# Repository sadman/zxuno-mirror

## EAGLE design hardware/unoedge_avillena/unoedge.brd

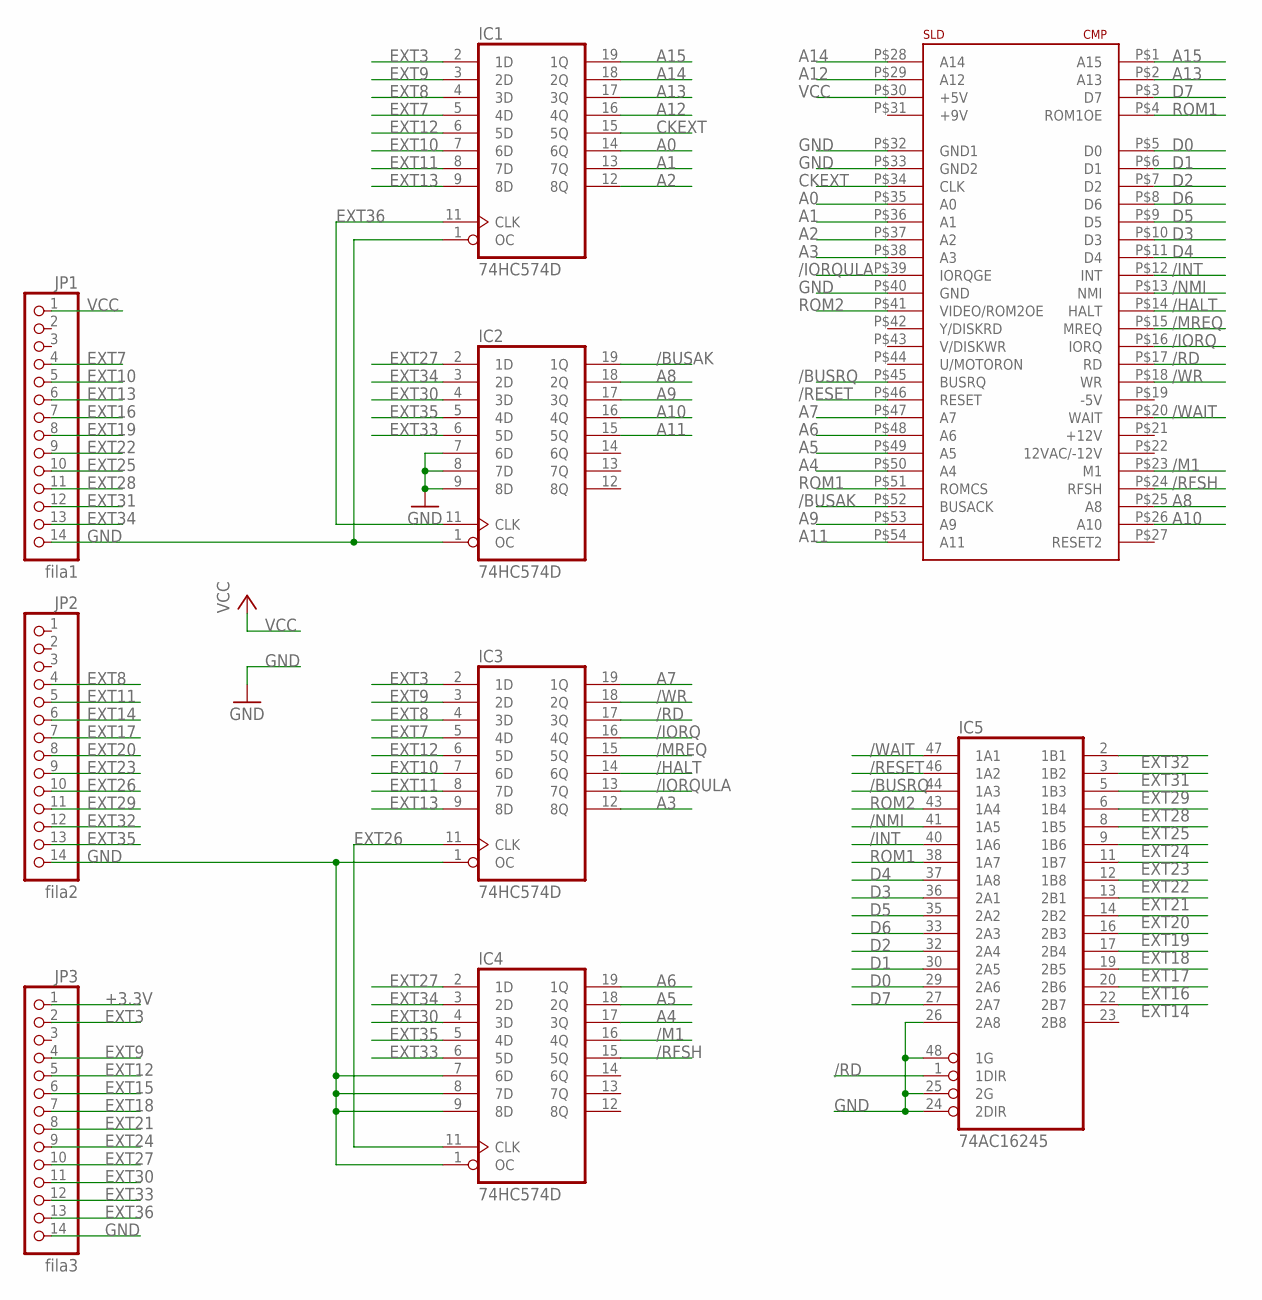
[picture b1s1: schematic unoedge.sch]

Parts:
IC1, IC2, IC3, IC4: 74HC574D; SO20W
IC5: 74AC16245; SSOP48DL
JP1: fila1; 1X14
JP2: fila2; 1X14
JP3: fila3; 1X14
U$2: CONECTOR_EDGE_LADO_SPECTRUM; CONECTOR_LADO_SPECTRUM

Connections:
+3.3V: JP3.1
/BUSAK: IC2.19 (1Q), U$2.P$52 (BUSACK)
/BUSRQ: IC5.44 (1A3), U$2.P$45 (BUSRQ)
/HALT: IC3.14 (6Q), U$2.P$14 (HALT)
/INT: IC5.40 (1A6), U$2.P$12 (INT)
/IORQ: IC3.16 (4Q), U$2.P$16 (IORQ)
/IORQULA: IC3.13 (7Q), U$2.P$39 (IORQGE)
/M1: IC4.16 (4Q), U$2.P$23 (M1)
/MREQ: IC3.15 (5Q), U$2.P$15 (MREQ)
/NMI: IC5.41 (1A5), U$2.P$13 (NMI)
/RD: IC3.17 (3Q), IC5.1 (1DIR), U$2.P$17 (RD)
/RESET: IC5.46 (1A2), U$2.P$46 (RESET)
/RFSH: IC4.15 (5Q), U$2.P$24 (RFSH)
/WAIT: IC5.47 (1A1), U$2.P$20 (WAIT)
/WR: IC3.18 (2Q), U$2.P$18 (WR)
A0: IC1.14 (6Q), U$2.P$35 (A0)
A1: IC1.13 (7Q), U$2.P$36 (A1)
A2: IC1.12 (8Q), U$2.P$37 (A2)
A3: IC3.12 (8Q), U$2.P$38 (A3)
A4: IC4.17 (3Q), U$2.P$50 (A4)
A5: IC4.18 (2Q), U$2.P$49 (A5)
A6: IC4.19 (1Q), U$2.P$48 (A6)
A7: IC3.19 (1Q), U$2.P$47 (A7)
A8: IC2.18 (2Q), U$2.P$25 (A8)
A9: IC2.17 (3Q), U$2.P$53 (A9)
A10: IC2.16 (4Q), U$2.P$26 (A10)
A11: IC2.15 (5Q), U$2.P$54 (A11)
A12: IC1.16 (4Q), U$2.P$29 (A12)
A13: IC1.17 (3Q), U$2.P$2 (A13)
A14: IC1.18 (2Q), U$2.P$28 (A14)
A15: IC1.19 (1Q), U$2.P$1 (A15)
CKEXT: IC1.15 (5Q), U$2.P$34 (CLK)
D0: IC5.29 (2A6), U$2.P$5 (D0)
D1: IC5.30 (2A5), U$2.P$6 (D1)
D2: IC5.32 (2A4), U$2.P$7 (D2)
D3: IC5.36 (2A1), U$2.P$10 (D3)
D4: IC5.37 (1A8), U$2.P$11 (D4)
D5: IC5.35 (2A2), U$2.P$9 (D5)
D6: IC5.33 (2A3), U$2.P$8 (D6)
D7: IC5.27 (2A7), U$2.P$3 (D7)
EXT3: IC1.2 (1D), IC3.2 (1D), JP3.2
EXT7: IC1.5 (4D), IC3.5 (4D), JP1.4
EXT8: IC1.4 (3D), IC3.4 (3D), JP2.4
EXT9: IC1.3 (2D), IC3.3 (2D), JP3.4
EXT10: IC1.7 (6D), IC3.7 (6D), JP1.5
EXT11: IC1.8 (7D), IC3.8 (7D), JP2.5
EXT12: IC1.6 (5D), IC3.6 (5D), JP3.5
EXT13: IC1.9 (8D), IC3.9 (8D), JP1.6
EXT14: IC5.22 (2B7), JP2.6
EXT15: JP3.6
EXT16: IC5.20 (2B6), JP1.7
EXT17: IC5.19 (2B5), JP2.7
EXT18: IC5.17 (2B4), JP3.7
EXT19: IC5.16 (2B3), JP1.8
EXT20: IC5.14 (2B2), JP2.8
EXT21: IC5.13 (2B1), JP3.8
EXT22: IC5.12 (1B8), JP1.9
EXT23: IC5.11 (1B7), JP2.9
EXT24: IC5.9 (1B6), JP3.9
EXT25: IC5.8 (1B5), JP1.10
EXT26: IC3.11 (CLK), IC4.11 (CLK), JP2.10
EXT27: IC2.2 (1D), IC4.2 (1D), JP3.10
EXT28: IC5.6 (1B4), JP1.11
EXT29: IC5.5 (1B3), JP2.11
EXT30: IC2.4 (3D), IC4.4 (3D), JP3.11
EXT31: IC5.3 (1B2), JP1.12
EXT32: IC5.2 (1B1), JP2.12
EXT33: IC2.6 (5D), IC4.6 (5D), JP3.12
EXT34: IC2.3 (2D), IC4.3 (2D), JP1.13
EXT35: IC2.5 (4D), IC4.5 (4D), JP2.13
EXT36: IC1.11 (CLK), IC2.11 (CLK), JP3.13
GND: IC1.1 (OC), IC1.10 (GND), IC2.1 (OC), IC2.7 (6D), IC2.8 (7D), IC2.9 (8D), IC2.10 (GND), IC3.1 (OC), IC3.10 (GND), IC4.1 (OC), IC4.7 (6D), IC4.8 (7D), IC4.9 (8D), IC4.10 (GND), IC5.4 (GND), IC5.10 (GND), IC5.15 (GND), IC5.21 (GND), IC5.24 (2DIR), IC5.25 (2G), IC5.26 (2A8), IC5.28 (GND), IC5.34 (GND), IC5.39 (GND), IC5.45 (GND), IC5.48 (1G), JP1.14, JP2.14, JP3.14, U$2.P$32 (GND1), U$2.P$33 (GND2), U$2.P$40 (GND)
ROM1: IC5.38 (1A7), U$2.P$4 (ROM1OE), U$2.P$51 (ROMCS)
ROM2: IC5.43 (1A4), U$2.P$41 (VIDEO/ROM2OE)
VCC: IC1.20 (VCC), IC2.20 (VCC), IC3.20 (VCC), IC4.20 (VCC), IC5.7 (VCC), IC5.18 (VCC), IC5.31 (VCC), IC5.42 (VCC), JP1.1, U$2.P$30 (+5V)

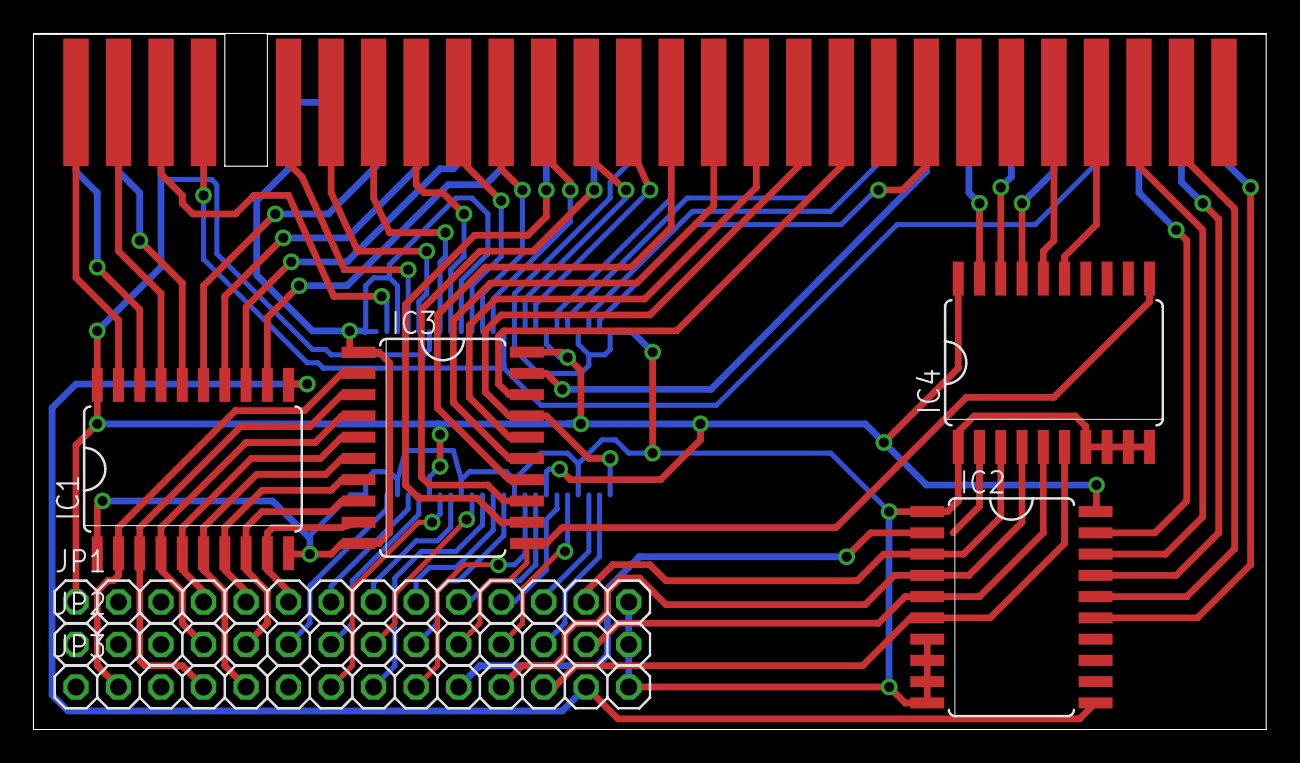
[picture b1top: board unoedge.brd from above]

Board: 2 copper layers, 73.7 x 41.6 mm, 9 parts (1 on the bottom side), 73 nets.

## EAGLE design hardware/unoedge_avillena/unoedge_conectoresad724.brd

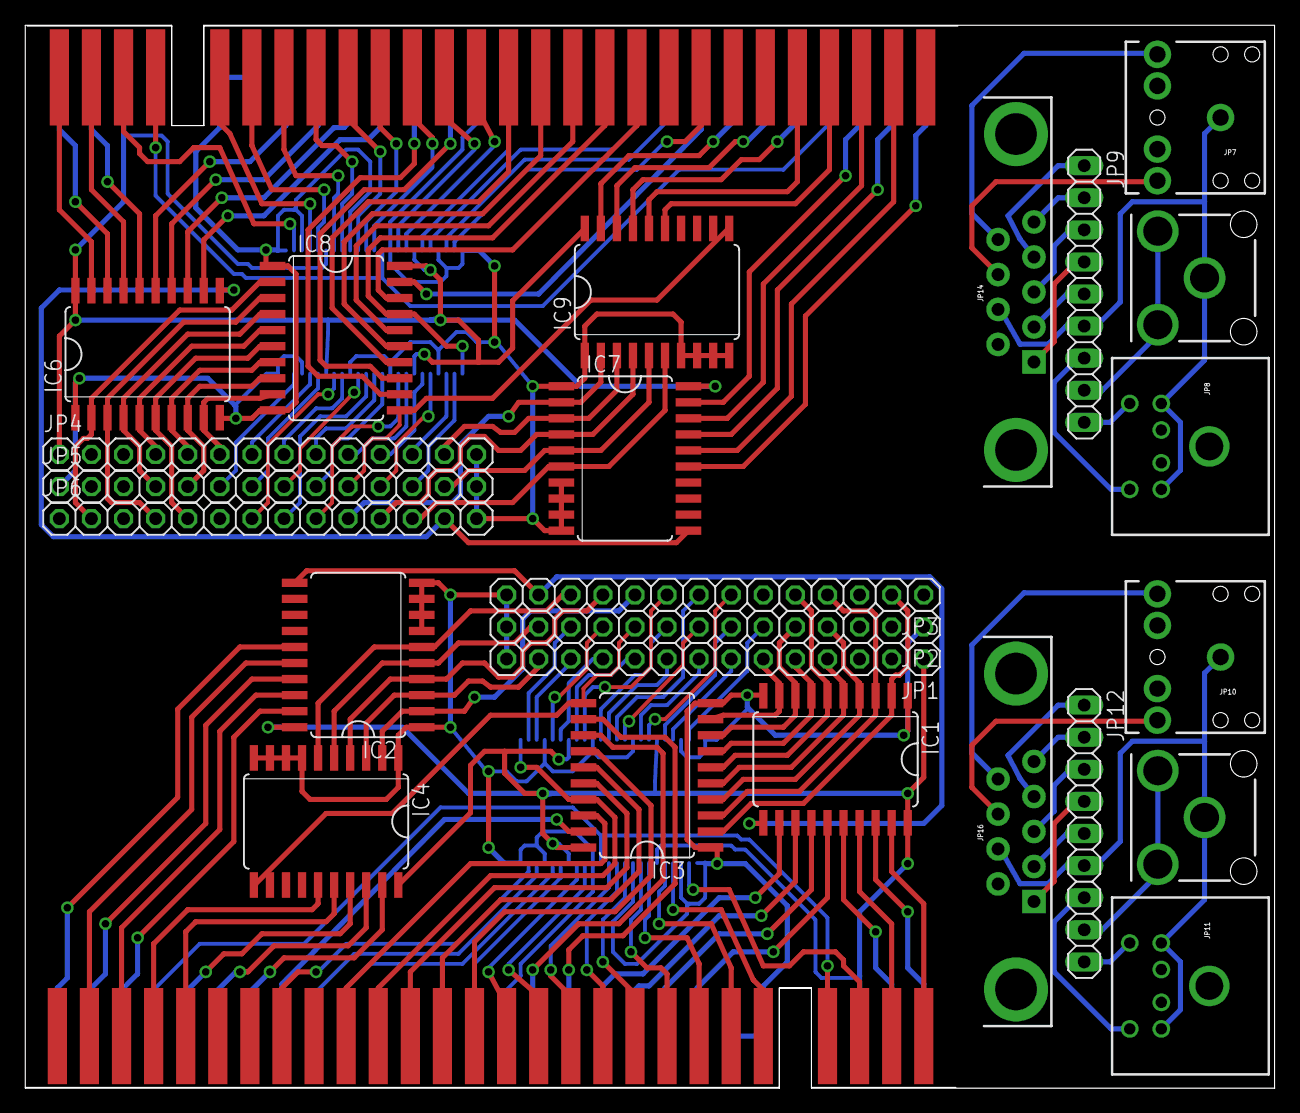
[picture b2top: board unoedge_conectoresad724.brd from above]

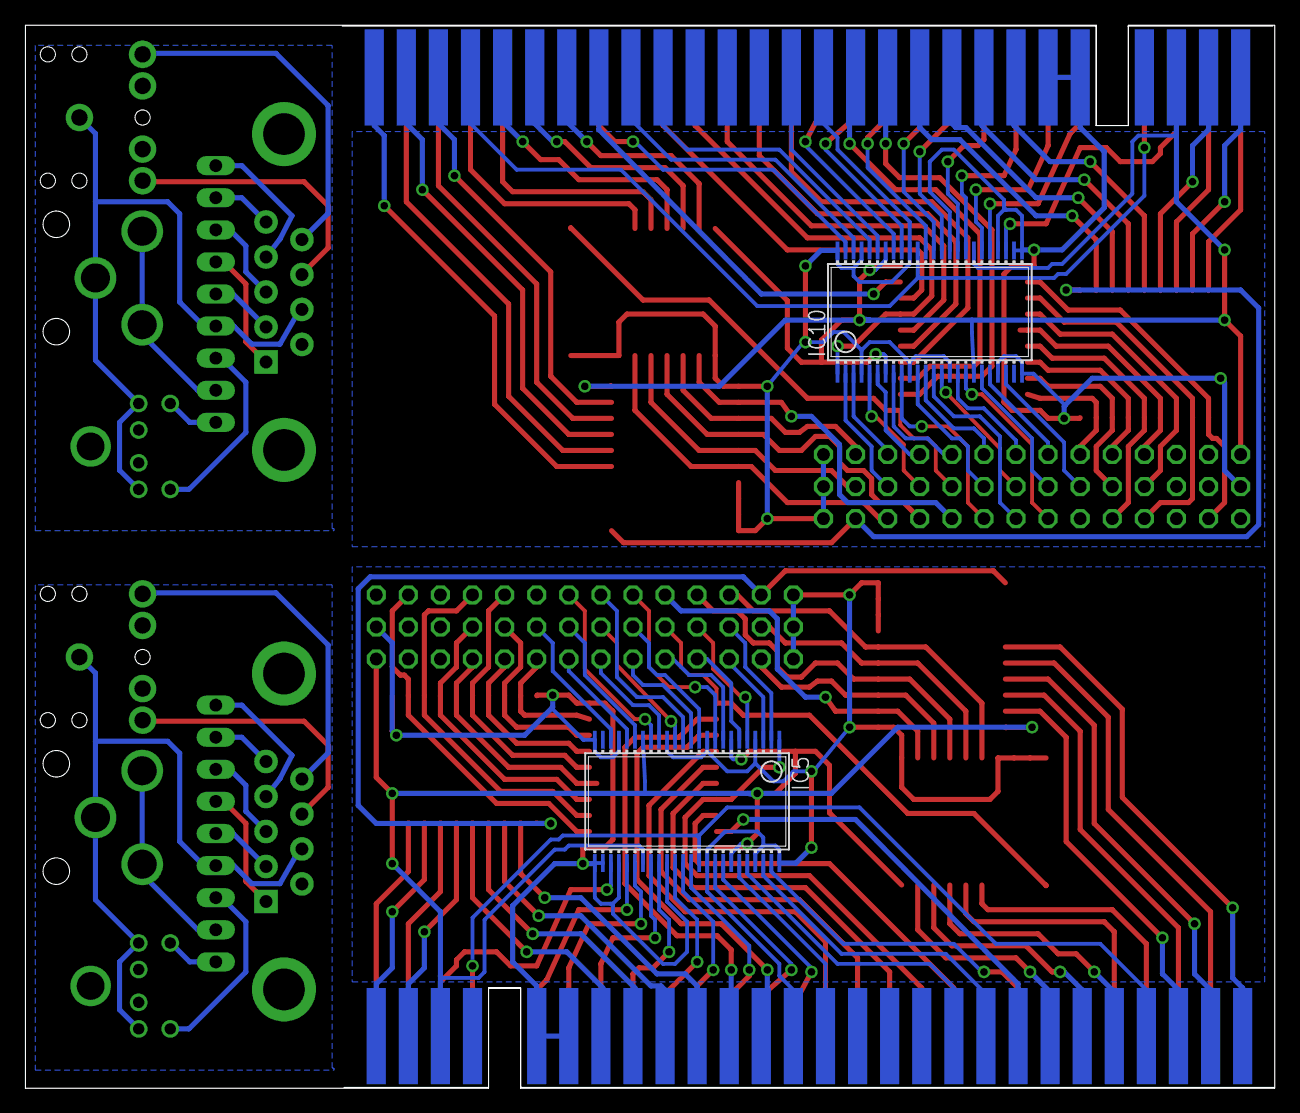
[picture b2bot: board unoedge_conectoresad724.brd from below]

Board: 2 copper layers, 98.9 x 84.1 mm, 28 parts (2 on the bottom side), 168 nets.

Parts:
IC1, IC2, IC3, IC4, IC6, IC7, IC8, IC9: 74HC574D; SO20W
IC5, IC10: 74AC16245; SSOP48DL
JP1, JP4: fila1; 1X14
JP2, JP5: fila2; 1X14
JP3, JP6: fila3; 1X14
JP7, JP10: AUDIO-JACK
JP8, JP11: MINI-DIN6PTH; MINI-DIN6
JP9, JP12: 1X09
JP13, JP15: RCA
JP14, JP16: DB9_MALE
U$1, U$2: CONECTOR_EDGE_LADO_SPECTRUM; CONECTOR_LADO_SPECTRUM

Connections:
/BUSAK: IC2.19, U$2.P$52
/BUSAK1: IC7.19, U$1.P$52
/BUSRQ: IC5.44, U$2.P$45
/BUSRQ1: IC10.44, U$1.P$45
/HALT: IC3.14, U$2.P$14
/HALT1: IC8.14, U$1.P$14
/INT: IC5.40, U$2.P$12
/INT1: IC10.40, U$1.P$12
/IORQ: IC3.16, U$2.P$16
/IORQ1: IC8.16, U$1.P$16
/IORQULA: IC3.13, U$2.P$39
/IORQULA1: IC8.13, U$1.P$39
/M1: IC4.16, U$2.P$23
/M2: IC9.16, U$1.P$23
/MREQ: IC3.15, U$2.P$15
/MREQ1: IC8.15, U$1.P$15
/NMI: IC5.41, U$2.P$13
/NMI1: IC10.41, U$1.P$13
/RD: IC3.17, IC5.1, U$2.P$17
/RD1: IC8.17, IC10.1, U$1.P$17
/RESET: IC5.46, U$2.P$46
/RESET1: IC10.46, U$1.P$46
/RFSH: IC4.15, U$2.P$24
/RFSH1: IC9.15, U$1.P$24
/WAIT: IC5.47, U$2.P$20
/WAIT1: IC10.47, U$1.P$20
/WR: IC3.18, U$2.P$18
/WR1: IC8.18, U$1.P$18
A0: IC1.14, U$2.P$35
A1: IC1.13, U$2.P$36
A2: IC1.12, U$2.P$37
A3: IC3.12, U$2.P$38
A4: IC4.17, U$2.P$50
A5: IC4.18, U$2.P$49
A6: IC4.19, U$2.P$48
A7: IC3.19, U$2.P$47
A8: IC2.18, U$2.P$25
A9: IC2.17, U$2.P$53
A10: IC2.16, U$2.P$26
A11: IC2.15, U$2.P$54
A12: IC1.16, U$2.P$29
A13: IC1.17, U$2.P$2
A14: IC1.18, U$2.P$28
A15: IC1.19, U$2.P$1
A16: IC6.14, U$1.P$35
A17: IC6.13, U$1.P$36
A18: IC6.12, U$1.P$37
A19: IC8.12, U$1.P$38
A20: IC9.17, U$1.P$50
A21: IC9.18, U$1.P$49
A22: IC9.19, U$1.P$48
A23: IC8.19, U$1.P$47
A24: IC7.18, U$1.P$25
A25: IC7.17, U$1.P$53
A26: IC7.16, U$1.P$26
A27: IC7.15, U$1.P$54
A28: IC6.16, U$1.P$29
A29: IC6.17, U$1.P$2
A30: IC6.18, U$1.P$28
A31: IC6.19, U$1.P$1
CKEXT: IC1.15, U$2.P$34
CKEXT1: IC6.15, U$1.P$34
D0: IC5.29, U$2.P$5
D1: IC5.30, U$2.P$6
D2: IC5.32, U$2.P$7
D3: IC5.36, U$2.P$10
D4: IC5.37, U$2.P$11
D5: IC5.35, U$2.P$9
D6: IC5.33, U$2.P$8
D7: IC5.27, U$2.P$3
D8: IC10.27, U$1.P$3
D9: IC10.33, U$1.P$8
D10: IC10.29, U$1.P$5
D11: IC10.30, U$1.P$6
D12: IC10.32, U$1.P$7
D13: IC10.35, U$1.P$9
D14: IC10.36, U$1.P$10
D15: IC10.37, U$1.P$11
EXT1: IC6.5, IC8.5, JP4.4
EXT2: IC6.7, IC8.7, JP4.5
EXT3: IC1.2, IC3.2, JP3.2
EXT4: IC6.9, IC8.9, JP4.6
EXT5: IC10.20, JP4.7
EXT6: IC10.16, JP4.8
EXT7: IC1.5, IC3.5, JP1.4
EXT8: IC1.4, IC3.4, JP2.4
EXT9: IC1.3, IC3.3, JP3.4
EXT10: IC1.7, IC3.7, JP1.5
EXT11: IC1.8, IC3.8, JP2.5
EXT12: IC1.6, IC3.6, JP3.5
EXT13: IC1.9, IC3.9, JP1.6
EXT14: IC5.22, JP2.6
EXT16: IC5.20, JP1.7
EXT17: IC5.19, JP2.7
EXT18: IC5.17, JP3.7
EXT19: IC5.16, JP1.8
EXT20: IC5.14, JP2.8
EXT21: IC5.13, JP3.8
EXT22: IC5.12, JP1.9
EXT23: IC5.11, JP2.9
EXT24: IC5.9, JP3.9
EXT25: IC5.8, JP1.10
EXT26: IC3.11, IC4.11, JP2.10
EXT27: IC2.2, IC4.2, JP3.10
EXT28: IC5.6, JP1.11
EXT29: IC5.5, JP2.11
EXT30: IC2.4, IC4.4, JP3.11
EXT31: IC5.3, JP1.12
EXT32: IC5.2, JP2.12
EXT33: IC2.6, IC4.6, JP3.12
EXT34: IC2.3, IC4.3, JP1.13
EXT35: IC2.5, IC4.5, JP2.13
EXT36: IC1.11, IC2.11, JP3.13
EXT37: IC10.12, JP4.9
EXT38: IC10.8, JP4.10
EXT39: IC10.6, JP4.11
EXT40: IC10.3, JP4.12
EXT41: IC7.3, IC9.3, JP4.13
EXT42: IC6.4, IC8.4, JP5.4
EXT43: IC6.8, IC8.8, JP5.5
EXT44: IC10.22, JP5.6
EXT45: IC10.19, JP5.7
EXT46: IC10.14, JP5.8
EXT47: IC10.11, JP5.9
EXT48: IC8.11, IC9.11, JP5.10
EXT49: IC10.2, JP5.12
EXT50: IC7.5, IC9.5, JP5.13
EXT51: IC7.2, IC9.2, JP6.10
EXT52: IC6.2, IC8.2, JP6.2
EXT53: IC6.3, IC8.3, JP6.4
EXT54: IC6.6, IC8.6, JP6.5
EXT56: IC10.17, JP6.7
EXT57: IC10.13, JP6.8
EXT58: IC10.9, JP6.9
EXT59: IC6.11, IC7.11, JP6.13
EXT60: IC7.6, IC9.6, JP6.12
EXT61: IC10.5, JP5.11
EXT62: IC7.4, IC9.4, JP6.11
GND: IC1.1, IC1.10, IC2.1, IC2.7, IC2.8, IC2.9, IC2.10, IC3.1, IC3.10, IC4.1, IC4.7, IC4.8, IC4.9, IC4.10, IC5.4, IC5.10, IC5.15, IC5.21, IC5.24, IC5.25, IC5.26, IC5.28, IC5.34, IC5.39, IC5.45, IC5.48, JP1.14, JP2.1, JP2.14, JP3.14, U$2.P$32, U$2.P$33, U$2.P$40
GND1: IC6.1, IC6.10, IC7.1, IC7.7, IC7.8, IC7.9, IC7.10, IC8.1, IC8.10, IC9.1, IC9.7, IC9.8, IC9.9, IC9.10, IC10.4, IC10.10, IC10.15, IC10.21, IC10.24, IC10.25, IC10.26, IC10.28, IC10.34, IC10.39, IC10.45, IC10.48, JP4.14, JP5.1, JP5.14, JP6.14, U$1.P$32, U$1.P$33, U$1.P$40
GND2: JP7.SLEEVE, JP8.3, JP8.4, JP9.6, JP13.SHELL, JP14.8
GND3: JP10.SLEEVE, JP11.3, JP11.4, JP12.6, JP15.SHELL, JP16.8
unnamed: JP9.2, JP14.1
unnamed: JP9.1, JP14.2
unnamed: JP9.3, JP14.3
unnamed: JP9.5, JP14.4
unnamed: JP9.4, JP14.5
unnamed: JP7.TIP, JP14.6
unnamed: JP7.RING, JP14.7
unnamed: JP12.2, JP16.1
unnamed: JP8.5, JP9.9
unnamed: JP9.8, JP13.PIN, JP13.SWITCH
unnamed: JP8.6, JP9.7
unnamed: JP12.1, JP16.2
unnamed: JP12.3, JP16.3
unnamed: JP12.5, JP16.4
unnamed: JP12.4, JP16.5
unnamed: JP10.TIP, JP16.6
unnamed: JP10.RING, JP16.7
unnamed: JP12.8, JP15.PIN, JP15.SWITCH
unnamed: JP11.5, JP12.9
unnamed: JP11.6, JP12.7
ROM1: IC5.38, U$2.P$4, U$2.P$51
ROM2: IC5.43, U$2.P$41
ROM3: IC10.43, U$1.P$41
ROM4: IC10.38, U$1.P$4, U$1.P$51
VCC: IC1.20, IC2.20, IC3.20, IC4.20, IC5.7, IC5.18, IC5.31, IC5.42, JP1.1, U$2.P$30
VCC1: IC6.20, IC7.20, IC8.20, IC9.20, IC10.7, IC10.18, IC10.31, IC10.42, JP4.1, U$1.P$30

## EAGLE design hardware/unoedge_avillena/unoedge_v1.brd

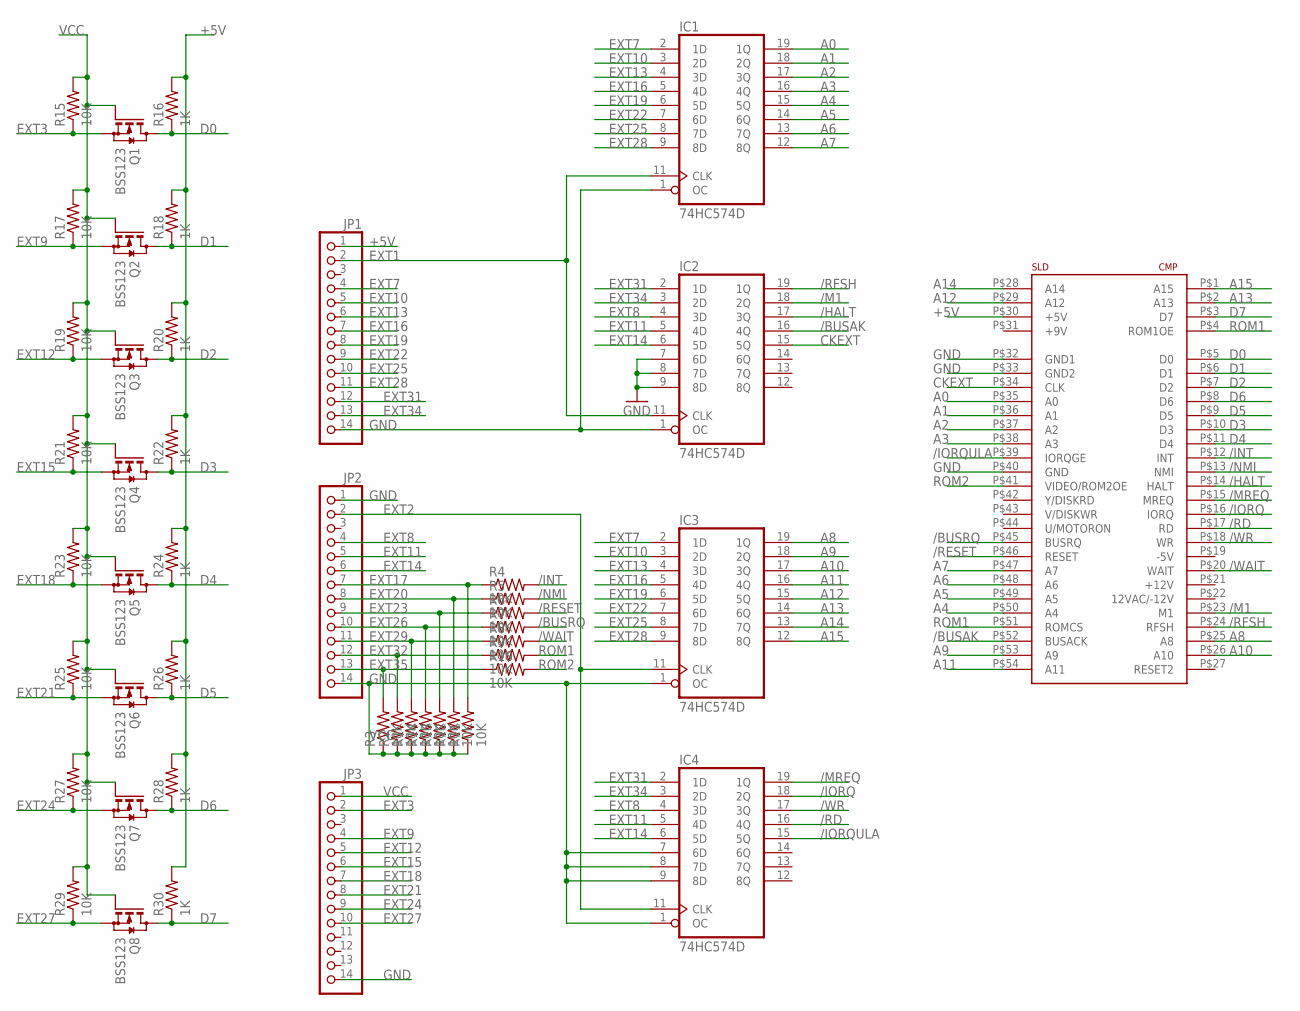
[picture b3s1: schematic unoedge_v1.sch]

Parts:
IC1, IC2, IC3, IC4: 74HC574D; SO20W
JP1, JP2, JP3: PINHD-1X14; 1X14
Q1, Q2, Q3, Q4, Q5, Q6, Q7, Q8: BSS123; SOT23
R1, R2, R3, R4, R5, R6, R7, R8, R9, R10, R11, R12, R13, R14, R15, R17, R19, R21, R23, R25, R27, R29: 10K; R0805
R16, R18, R20, R22, R24, R26, R28, R30: 1K; R0805
U$2: CONECTOR_EDGE_LADO_SPECTRUM; CONECTOR_LADO_SPECTRUM

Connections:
+5V: JP1.1, R16.2, R18.2, R20.2, R22.2, R24.2, R26.2, R28.2, R30.2, U$2.P$30 (+5V)
/BUSAK: IC2.16 (4Q), U$2.P$52 (BUSACK)
/BUSRQ: R7.2, U$2.P$45 (BUSRQ)
/HALT: IC2.17 (3Q), U$2.P$14 (HALT)
/INT: R4.2, U$2.P$12 (INT)
/IORQ: IC4.18 (2Q), U$2.P$16 (IORQ)
/IORQULA: IC4.15 (5Q), U$2.P$39 (IORQGE)
/M1: IC2.18 (2Q), U$2.P$23 (M1)
/MREQ: IC4.19 (1Q), U$2.P$15 (MREQ)
/NMI: R5.2, U$2.P$13 (NMI)
/RD: IC4.16 (4Q), U$2.P$17 (RD)
/RESET: R6.2, U$2.P$46 (RESET)
/RFSH: IC2.19 (1Q), U$2.P$24 (RFSH)
/WAIT: R8.2, U$2.P$20 (WAIT)
/WR: IC4.17 (3Q), U$2.P$18 (WR)
A0: IC1.19 (1Q), U$2.P$35 (A0)
A1: IC1.18 (2Q), U$2.P$36 (A1)
A2: IC1.17 (3Q), U$2.P$37 (A2)
A3: IC1.16 (4Q), U$2.P$38 (A3)
A4: IC1.15 (5Q), U$2.P$50 (A4)
A5: IC1.14 (6Q), U$2.P$49 (A5)
A6: IC1.13 (7Q), U$2.P$48 (A6)
A7: IC1.12 (8Q), U$2.P$47 (A7)
A8: IC3.19 (1Q), U$2.P$25 (A8)
A9: IC3.18 (2Q), U$2.P$53 (A9)
A10: IC3.17 (3Q), U$2.P$26 (A10)
A11: IC3.16 (4Q), U$2.P$54 (A11)
A12: IC3.15 (5Q), U$2.P$29 (A12)
A13: IC3.14 (6Q), U$2.P$2 (A13)
A14: IC3.13 (7Q), U$2.P$28 (A14)
A15: IC3.12 (8Q), U$2.P$1 (A15)
CKEXT: IC2.15 (5Q), U$2.P$34 (CLK)
D0: Q1.3 (D), R16.1, U$2.P$5 (D0)
D1: Q2.3 (D), R18.1, U$2.P$6 (D1)
D2: Q3.3 (D), R20.1, U$2.P$7 (D2)
D3: Q4.3 (D), R22.1, U$2.P$10 (D3)
D4: Q5.3 (D), R24.1, U$2.P$11 (D4)
D5: Q6.3 (D), R26.1, U$2.P$9 (D5)
D6: Q7.3 (D), R28.1, U$2.P$8 (D6)
D7: Q8.3 (D), R30.1, U$2.P$3 (D7)
EXT1: IC1.11 (CLK), IC2.11 (CLK), JP1.2
EXT2: IC3.11 (CLK), IC4.11 (CLK), JP2.2
EXT3: JP3.2, Q1.2 (S), R15.1
EXT7: IC1.2 (1D), IC3.2 (1D), JP1.4
EXT8: IC2.4 (3D), IC4.4 (3D), JP2.4
EXT9: JP3.4, Q2.2 (S), R17.1
EXT10: IC1.3 (2D), IC3.3 (2D), JP1.5
EXT11: IC2.5 (4D), IC4.5 (4D), JP2.5
EXT12: JP3.5, Q3.2 (S), R19.1
EXT13: IC1.4 (3D), IC3.4 (3D), JP1.6
EXT14: IC2.6 (5D), IC4.6 (5D), JP2.6
EXT15: JP3.6, Q4.2 (S), R21.1
EXT16: IC1.5 (4D), IC3.5 (4D), JP1.7
EXT17: JP2.7, R4.1, R11.2
EXT18: JP3.7, Q5.2 (S), R23.1
EXT19: IC1.6 (5D), IC3.6 (5D), JP1.8
EXT20: JP2.8, R5.1, R12.2
EXT21: JP3.8, Q6.2 (S), R25.1
EXT22: IC1.7 (6D), IC3.7 (6D), JP1.9
EXT23: JP2.9, R6.1, R13.2
EXT24: JP3.9, Q7.2 (S), R27.1
EXT25: IC1.8 (7D), IC3.8 (7D), JP1.10
EXT26: JP2.10, R7.1, R14.2
EXT27: JP3.10, Q8.2 (S), R29.1
EXT28: IC1.9 (8D), IC3.9 (8D), JP1.11
EXT29: JP2.11, R1.2, R8.1
EXT31: IC2.2 (1D), IC4.2 (1D), JP1.12
EXT32: JP2.12, R2.2, R9.1
EXT34: IC2.3 (2D), IC4.3 (2D), JP1.13
EXT35: JP2.13, R3.2, R10.1
GND: IC1.1 (OC), IC1.10 (GND), IC2.1 (OC), IC2.7 (6D), IC2.8 (7D), IC2.10 (GND), IC3.1 (OC), IC3.10 (GND), IC4.1 (OC), IC4.7 (6D), IC4.8 (7D), IC4.9 (8D), IC4.10 (GND), JP1.14, JP2.1, JP2.14, JP3.14, R1.1, R2.1, R3.1, R11.1, R12.1, R13.1, R14.1, U$2.P$32 (GND1), U$2.P$33 (GND2), U$2.P$40 (GND)
ROM1: R9.2, U$2.P$4 (ROM1OE), U$2.P$51 (ROMCS)
ROM2: R10.2, U$2.P$41 (VIDEO/ROM2OE)
VCC: IC1.20 (VCC), IC2.20 (VCC), IC3.20 (VCC), IC4.20 (VCC), JP3.1, Q1.1 (G), Q2.1 (G), Q3.1 (G), Q4.1 (G), Q5.1 (G), Q6.1 (G), Q7.1 (G), Q8.1 (G), R15.2, R17.2, R19.2, R21.2, R23.2, R25.2, R27.2, R29.2

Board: 2 copper layers, 46 parts (0 on the bottom side), 74 nets, no tracks yet.

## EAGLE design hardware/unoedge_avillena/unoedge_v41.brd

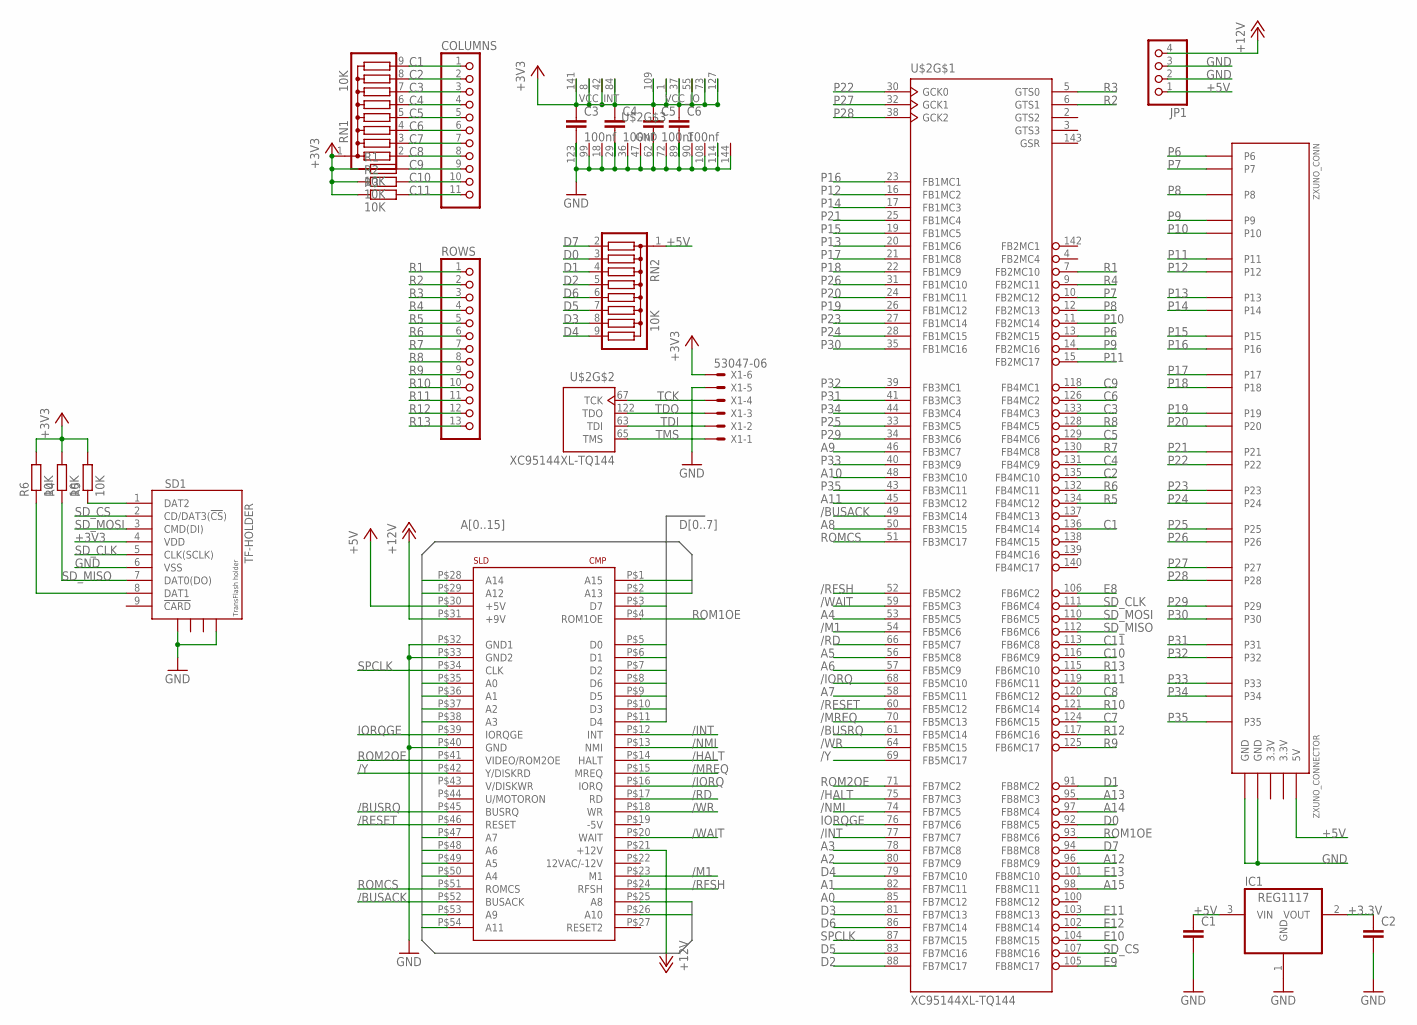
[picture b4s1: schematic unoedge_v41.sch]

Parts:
C1, C2: C-EUC0805; C0805
C3, C4, C5, C6: 100nf; C0603
COLUMNS: PINHD-1X11; 1X11
IC1: REG1117; SOT223
JP1: PINHD-1X4; 1X04
R1, R2, R3, R4, R5, R6: 10K; R0603
RN1, RN2: 10K; SIL9
ROWS: PINHD-1X13; 1X13
SD1: TF-HOLDER; TF-PULL
U$1: CONECTOR_EDGE_LADO_SPECTRUM; CONECTOR_LADO_SPECTRUM
U$2: XC95144XL-TQ144; TQ144
X1: 53047-06
ZXUNO_CONN: ZXUNO_CONNECTOR

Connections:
3.3V: ZXUNO_CONN.3.3V@1 (3.3V), ZXUNO_CONN.3.3V@2 (3.3V)
+5V: C1.1, IC1.3 (VIN), JP1.1, RN2.1, U$1.P$30 (+5V), ZXUNO_CONN.5V
+12V: JP1.4, U$1.P$21 (+12V), U$1.P$31 (+9V)
/BUSACK: U$1.P$52 (BUSACK), U$2.49 (FB3MC14)
/BUSRQ: U$1.P$45 (BUSRQ), U$2.61 (FB5MC14)
/HALT: U$1.P$14 (HALT), U$2.75 (FB7MC3)
/INT: U$1.P$12 (INT), U$2.77 (FB7MC7)
/IORQ: U$1.P$16 (IORQ), U$2.68 (FB5MC10)
/M1: U$1.P$23 (M1), U$2.54 (FB5MC6)
/MREQ: U$1.P$15 (MREQ), U$2.70 (FB5MC13)
/NMI: U$1.P$13 (NMI), U$2.74 (FB7MC5)
/RD: U$1.P$17 (RD), U$2.66 (FB5MC7)
/RESET: U$1.P$46 (RESET), U$2.60 (FB5MC12)
/RFSH: U$1.P$24 (RFSH), U$2.52 (FB5MC2)
/WAIT: U$1.P$20 (WAIT), U$2.59 (FB5MC3)
/WR: U$1.P$18 (WR), U$2.64 (FB5MC15)
/Y: U$1.P$42 (Y/DISKRD), U$2.69 (FB5MC17)
A0: U$1.P$35 (A0), U$2.85 (FB7MC12)
A1: U$1.P$36 (A1), U$2.82 (FB7MC11)
A2: U$1.P$37 (A2), U$2.80 (FB7MC9)
A3: U$1.P$38 (A3), U$2.78 (FB7MC8)
A4: U$1.P$50 (A4), U$2.53 (FB5MC5)
A5: U$1.P$49 (A5), U$2.56 (FB5MC8)
A6: U$1.P$48 (A6), U$2.57 (FB5MC9)
A7: U$1.P$47 (A7), U$2.58 (FB5MC11)
A8: U$1.P$25 (A8), U$2.50 (FB3MC15)
A9: U$1.P$53 (A9), U$2.46 (FB3MC7)
A10: U$1.P$26 (A10), U$2.48 (FB3MC10)
A11: U$1.P$54 (A11), U$2.45 (FB3MC12)
A12: U$1.P$29 (A12), U$2.96 (FB8MC9)
A13: U$1.P$2 (A13), U$2.95 (FB8MC3)
A14: U$1.P$28 (A14), U$2.97 (FB8MC4)
A15: U$1.P$1 (A15), U$2.98 (FB8MC11)
C1: COLUMNS.1, RN1.9, U$2.136 (FB4MC14)
C2: COLUMNS.2, RN1.8, U$2.135 (FB4MC10)
C3: COLUMNS.3, RN1.7, U$2.133 (FB4MC3)
C4: COLUMNS.4, RN1.6, U$2.131 (FB4MC9)
C5: COLUMNS.5, RN1.5, U$2.129 (FB4MC6)
C6: COLUMNS.6, RN1.4, U$2.126 (FB4MC2)
C7: COLUMNS.7, RN1.3, U$2.124 (FB6MC15)
C8: COLUMNS.8, RN1.2, U$2.120 (FB6MC12)
C9: COLUMNS.9, R1.2, U$2.118 (FB4MC1)
C10: COLUMNS.10, R2.2, U$2.116 (FB6MC9)
C11: COLUMNS.11, R3.2, U$2.113 (FB6MC8)
D0: RN2.3, U$1.P$5 (D0), U$2.92 (FB8MC5)
D1: RN2.4, U$1.P$6 (D1), U$2.91 (FB8MC2)
D2: RN2.5, U$1.P$7 (D2), U$2.88 (FB7MC17)
D3: RN2.8, U$1.P$10 (D3), U$2.81 (FB7MC13)
D4: RN2.9, U$1.P$11 (D4), U$2.79 (FB7MC10)
D5: RN2.7, U$1.P$9 (D5), U$2.83 (FB7MC16)
D6: RN2.6, U$1.P$8 (D6), U$2.86 (FB7MC14)
D7: RN2.2, U$1.P$3 (D7), U$2.94 (FB8MC8)
E8: U$2.106 (FB6MC2)
E9: U$2.105 (FB8MC17)
E10: U$2.104 (FB8MC15)
E11: U$2.103 (FB8MC13)
E12: U$2.102 (FB8MC14)
E13: U$2.101 (FB8MC10)
GND: C1.2, C2.2, C3.2, C4.2, C5.2, C6.2, IC1.1 (GND), JP1.2, JP1.3, SD1.6 (VSS), SD1.S1, SD1.S4, U$1.P$32 (GND1), U$1.P$33 (GND2), U$1.P$40 (GND), U$2.18 (GND), U$2.29 (GND), U$2.36 (GND), U$2.47 (GND), U$2.62 (GND), U$2.72 (GND), U$2.89 (GND), U$2.90 (GND), U$2.99 (GND), U$2.108 (GND), U$2.114 (GND), U$2.123 (GND), U$2.144 (GND), X1.2, ZXUNO_CONN.GND@1 (GND), ZXUNO_CONN.GND@2 (GND)
IORQGE: U$1.P$39 (IORQGE), U$2.76 (FB7MC6)
unnamed: R6.1, SD1.8 (DAT1)
unnamed: R5.1, SD1.1 (DAT2)
P6: U$2.13 (FB2MC15), ZXUNO_CONN.P6
P7: U$2.10 (FB2MC12), ZXUNO_CONN.P7
P8: U$2.12 (FB2MC13), ZXUNO_CONN.P8
P9: U$2.14 (FB2MC16), ZXUNO_CONN.P9
P10: U$2.11 (FB2MC14), ZXUNO_CONN.P10
P11: U$2.15 (FB2MC17), ZXUNO_CONN.P11
P12: U$2.16 (FB1MC2), ZXUNO_CONN.P12
P13: U$2.20 (FB1MC6), ZXUNO_CONN.P13
P14: U$2.17 (FB1MC3), ZXUNO_CONN.P14
P15: U$2.19 (FB1MC5), ZXUNO_CONN.P15
P16: U$2.23 (FB1MC1), ZXUNO_CONN.P16
P17: U$2.21 (FB1MC8), ZXUNO_CONN.P17
P18: U$2.22 (FB1MC9), ZXUNO_CONN.P18
P19: U$2.26 (FB1MC12), ZXUNO_CONN.P19
P20: U$2.24 (FB1MC11), ZXUNO_CONN.P20
P21: U$2.25 (FB1MC4), ZXUNO_CONN.P21
P22: U$2.30 (GCK0), ZXUNO_CONN.P22
P23: U$2.27 (FB1MC14), ZXUNO_CONN.P23
P24: U$2.28 (FB1MC15), ZXUNO_CONN.P24
P25: U$2.33 (FB3MC5), ZXUNO_CONN.P25
P26: U$2.31 (FB1MC10), ZXUNO_CONN.P26
P27: U$2.32 (GCK1), ZXUNO_CONN.P27
P28: U$2.38 (GCK2), ZXUNO_CONN.P28
P29: U$2.34 (FB3MC6), ZXUNO_CONN.P29
P30: U$2.35 (FB1MC16), ZXUNO_CONN.P30
P31: U$2.41 (FB3MC3), ZXUNO_CONN.P31
P32: U$2.39 (FB3MC1), ZXUNO_CONN.P32
P33: U$2.40 (FB3MC9), ZXUNO_CONN.P33
P34: U$2.44 (FB3MC4), ZXUNO_CONN.P34
P35: U$2.43 (FB3MC11), ZXUNO_CONN.P35
R1: ROWS.1, U$2.7 (FB2MC10)
R2: ROWS.2, U$2.6 (GTS1)
R3: ROWS.3, U$2.5 (GTS0)
R4: ROWS.4, U$2.9 (FB2MC11)
R5: ROWS.5, U$2.134 (FB4MC12)
R6: ROWS.6, U$2.132 (FB4MC11)
R7: ROWS.7, U$2.130 (FB4MC8)
R8: ROWS.8, U$2.128 (FB4MC5)
R9: ROWS.9, U$2.125 (FB6MC17)
R10: ROWS.10, U$2.121 (FB6MC14)
R11: ROWS.11, U$2.119 (FB6MC11)
R12: ROWS.12, U$2.117 (FB6MC16)
R13: ROWS.13, U$2.115 (FB6MC10)
ROM1OE: U$1.P$4 (ROM1OE), U$2.93 (FB8MC6)
ROM2OE: U$1.P$41 (VIDEO/ROM2OE), U$2.71 (FB7MC2)
ROMCS: U$1.P$51 (ROMCS), U$2.51 (FB3MC17)
SD_CLK: SD1.5 (CLK(SCLK)), U$2.111 (FB6MC4)
SD_CS: SD1.2 (CD/DAT3(!CS!)), U$2.107 (FB8MC16)
SD_MISO: R4.1, SD1.7 (DAT0(DO)), U$2.112 (FB6MC6)
SD_MOSI: SD1.3 (CMD(DI)), U$2.110 (FB6MC5)
SPCLK: U$1.P$34 (CLK), U$2.87 (FB7MC15)
TCK: U$2.67 (TCK), X1.3
TDI: U$2.63 (TDI), X1.5
TDO: U$2.122 (TDO), X1.4
TMS: U$2.65 (TMS), X1.6

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
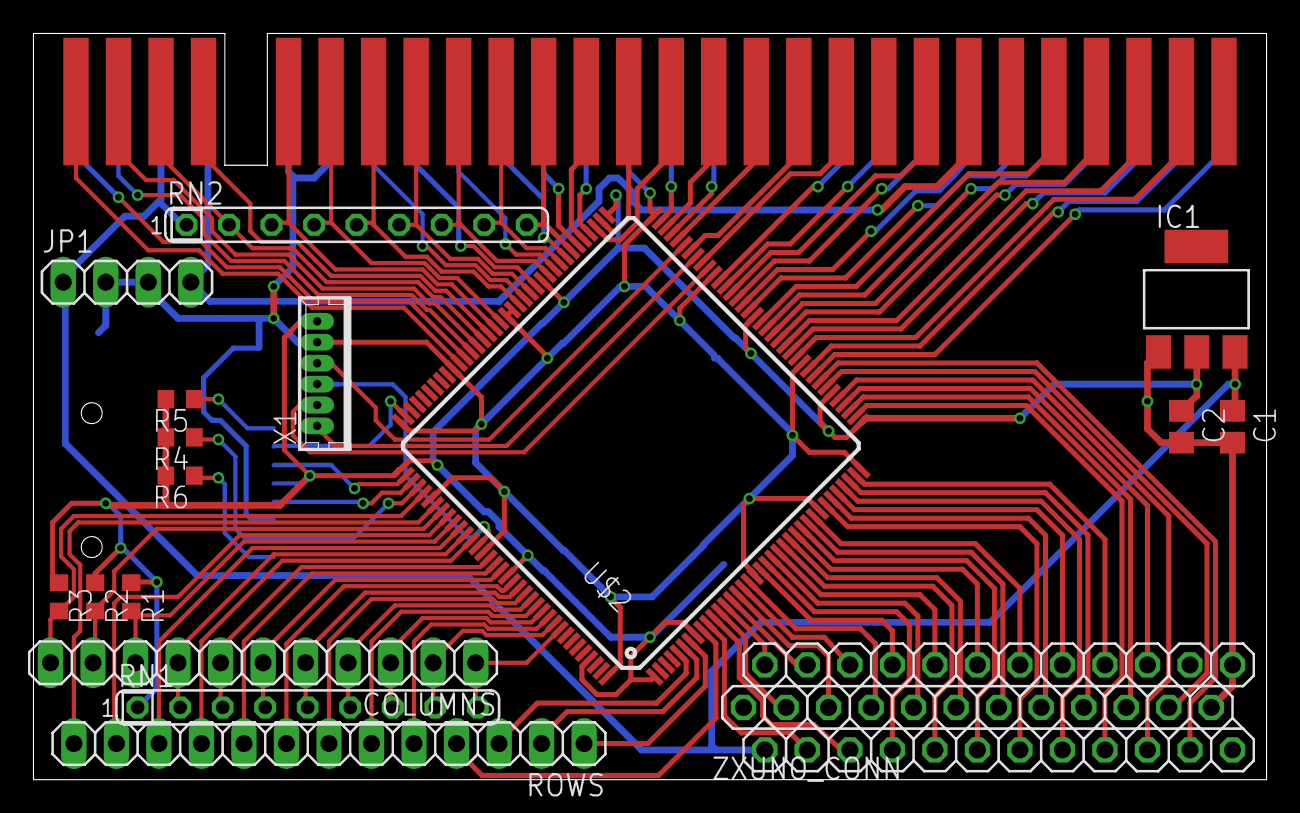
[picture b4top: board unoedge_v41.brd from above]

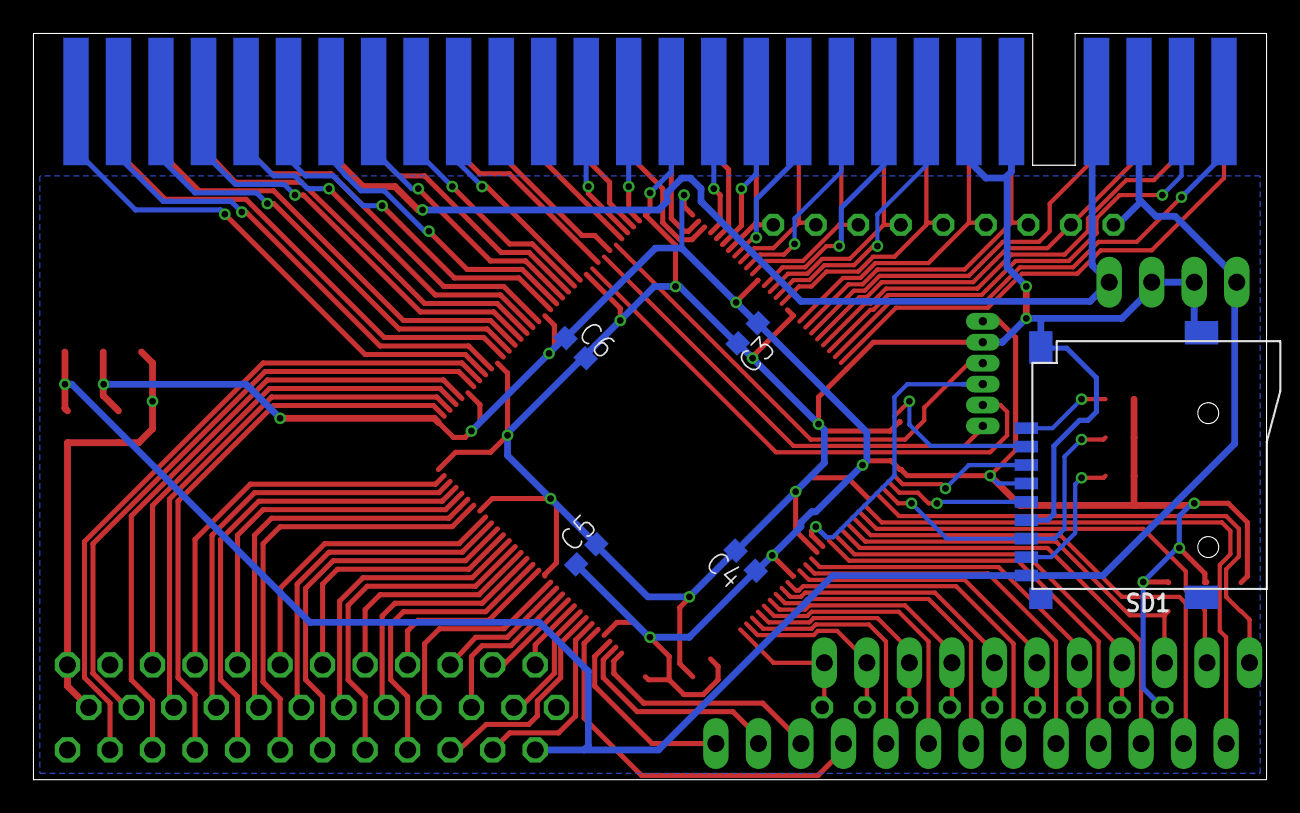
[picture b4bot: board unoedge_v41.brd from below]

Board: 2 copper layers, 73.7 x 44.6 mm, 23 parts (5 on the bottom side), 112 nets.

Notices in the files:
parts and their libraries:
SparkFun-Connectors: Licensing: Creative Commons ShareAlike 4.0 International - https://creativecommons.org/licenses/by-sa/4.0
